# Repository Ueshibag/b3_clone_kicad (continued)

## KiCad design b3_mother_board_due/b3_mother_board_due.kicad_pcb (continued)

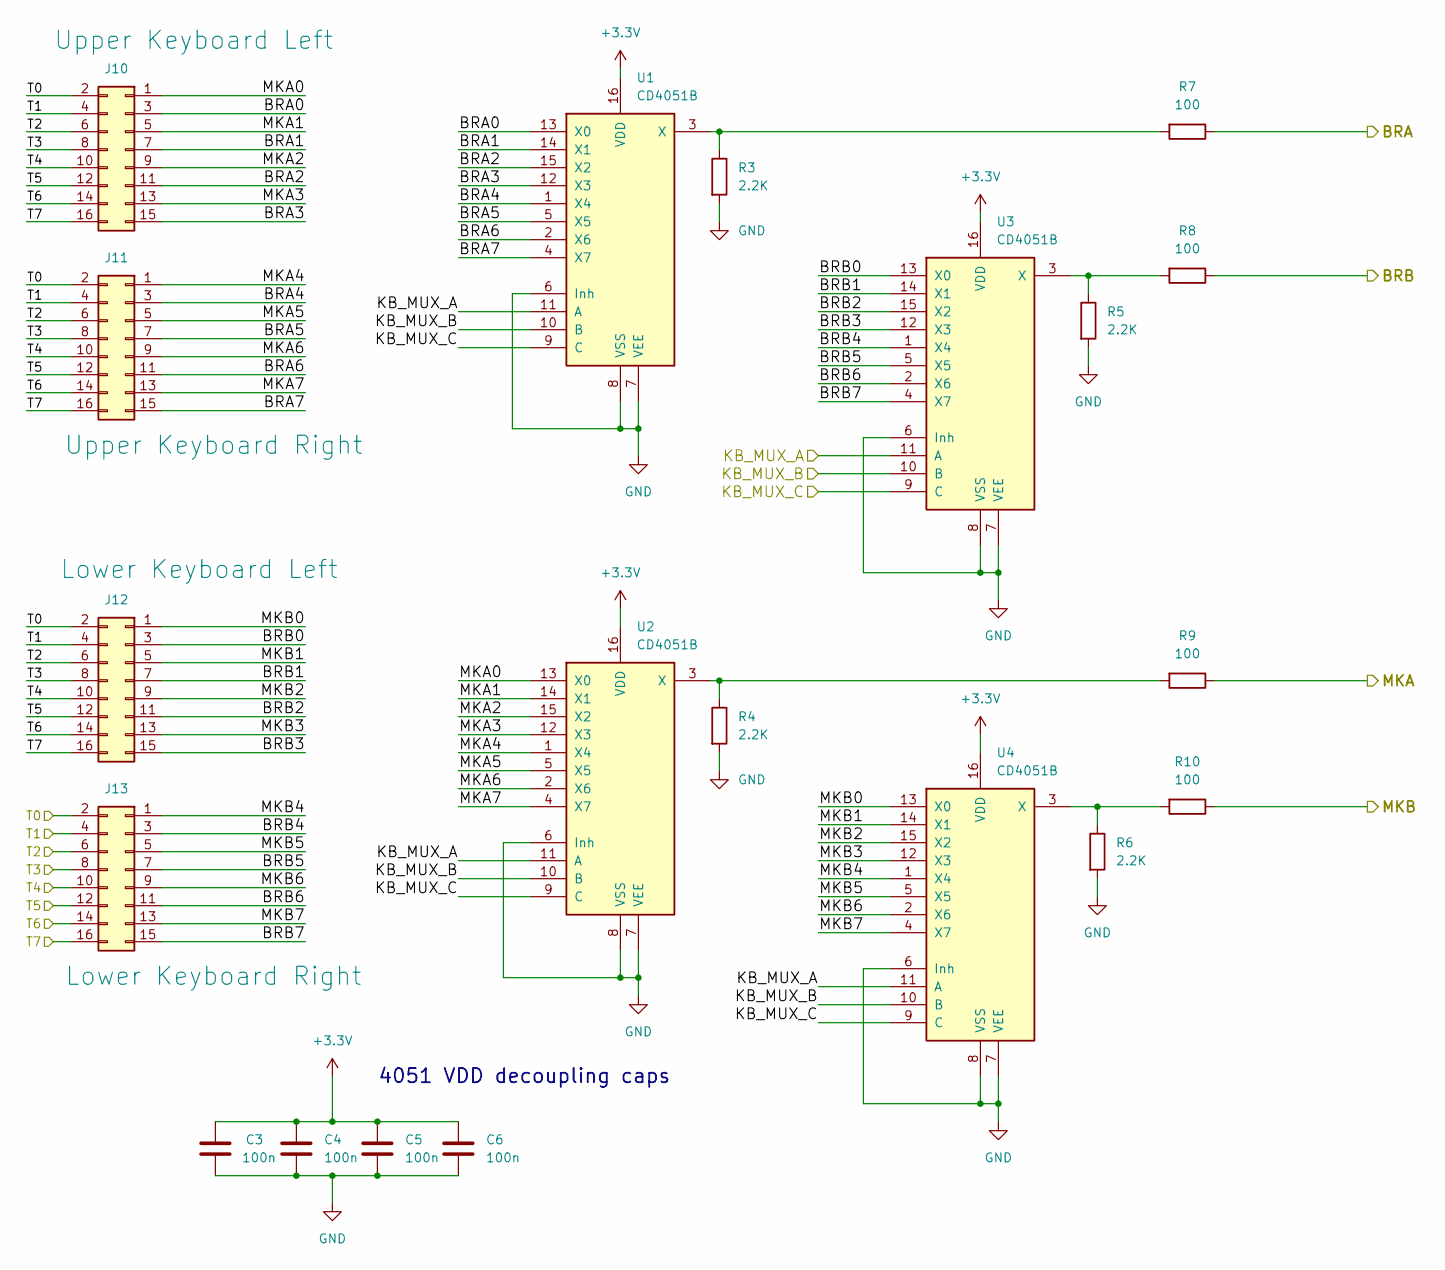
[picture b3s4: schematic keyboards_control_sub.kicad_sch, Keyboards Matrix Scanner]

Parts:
C3, C4, C5, C6: 100n; C_Rect_L11.5mm_W4.3mm_P10.00mm_MKT
J10: Upper Keyboard Left; IDC-Header_2x08_P2.54mm_Vertical
J11: Upper Keyboard Right; IDC-Header_2x08_P2.54mm_Vertical
J12: Lower Keyboard Left; IDC-Header_2x08_P2.54mm_Vertical
J13: Lower Keyboard Right; IDC-Header_2x08_P2.54mm_Vertical
R3, R4, R5, R6: 2.2K; R_Axial_DIN0207_L6.3mm_D2.5mm_P7.62mm_Horizontal
R7, R8, R9, R10: 100; R_Axial_DIN0207_L6.3mm_D2.5mm_P7.62mm_Horizontal
U1, U2, U3, U4: CD4051B; DIP-16_W7.62mm

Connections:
+3.3V: C3.1, C4.1, C5.1, C6.1, U1.16 (VDD), U2.16 (VDD), U3.16 (VDD), U4.16 (VDD); also elsewhere on the board
/T0: J10.2, J11.2, J12.2, J13.2; also elsewhere on the board
/T1: J10.4, J11.4, J12.4, J13.4; also elsewhere on the board
/T2: J10.6, J11.6, J12.6, J13.6; also elsewhere on the board
/T3: J10.8, J11.8, J12.8, J13.8; also elsewhere on the board
/T4: J10.10, J11.10, J12.10, J13.10; also elsewhere on the board
/T5: J10.12, J11.12, J12.12, J13.12; also elsewhere on the board
/T6: J10.14, J11.14, J12.14, J13.14; also elsewhere on the board
/T7: J10.16, J11.16, J12.16, J13.16; also elsewhere on the board
/keyboards_control_sub/BRA: R7.1; also elsewhere on the board
/keyboards_control_sub/BRA0: J10.3, U1.13 (X0)
/keyboards_control_sub/BRA1: J10.7, U1.14 (X1)
/keyboards_control_sub/BRA2: J10.11, U1.15 (X2)
/keyboards_control_sub/BRA3: J10.15, U1.12 (X3)
/keyboards_control_sub/BRA4: J11.3, U1.1 (X4)
/keyboards_control_sub/BRA5: J11.7, U1.5 (X5)
/keyboards_control_sub/BRA6: J11.11, U1.2 (X6)
/keyboards_control_sub/BRA7: J11.15, U1.4 (X7)
/keyboards_control_sub/BRB: R8.1; also elsewhere on the board
/keyboards_control_sub/BRB0: J12.3, U3.13 (X0)
/keyboards_control_sub/BRB1: J12.7, U3.14 (X1)
/keyboards_control_sub/BRB2: J12.11, U3.15 (X2)
/keyboards_control_sub/BRB3: J12.15, U3.12 (X3)
/keyboards_control_sub/BRB4: J13.3, U3.1 (X4)
/keyboards_control_sub/BRB5: J13.7, U3.5 (X5)
/keyboards_control_sub/BRB6: J13.11, U3.2 (X6)
/keyboards_control_sub/BRB7: J13.15, U3.4 (X7)
/keyboards_control_sub/KB_MUX_A: U1.11 (A), U2.11 (A), U3.11 (A), U4.11 (A); also elsewhere on the board
/keyboards_control_sub/KB_MUX_B: U1.10 (B), U2.10 (B), U3.10 (B), U4.10 (B); also elsewhere on the board
/keyboards_control_sub/KB_MUX_C: U1.9 (C), U2.9 (C), U3.9 (C), U4.9 (C); also elsewhere on the board
/keyboards_control_sub/MKA: R9.1; also elsewhere on the board
/keyboards_control_sub/MKA0: J10.1, U2.13 (X0)
/keyboards_control_sub/MKA1: J10.5, U2.14 (X1)
/keyboards_control_sub/MKA2: J10.9, U2.15 (X2)
/keyboards_control_sub/MKA3: J10.13, U2.12 (X3)
/keyboards_control_sub/MKA4: J11.1, U2.1 (X4)
/keyboards_control_sub/MKA5: J11.5, U2.5 (X5)
/keyboards_control_sub/MKA6: J11.9, U2.2 (X6)
/keyboards_control_sub/MKA7: J11.13, U2.4 (X7)
/keyboards_control_sub/MKB: R10.1; also elsewhere on the board
/keyboards_control_sub/MKB0: J12.1, U4.13 (X0)
/keyboards_control_sub/MKB1: J12.5, U4.14 (X1)
/keyboards_control_sub/MKB2: J12.9, U4.15 (X2)
/keyboards_control_sub/MKB3: J12.13, U4.12 (X3)
/keyboards_control_sub/MKB4: J13.1, U4.1 (X4)
/keyboards_control_sub/MKB5: J13.5, U4.5 (X5)
/keyboards_control_sub/MKB6: J13.9, U4.2 (X6)
/keyboards_control_sub/MKB7: J13.13, U4.4 (X7)
GND: C3.2, C4.2, C5.2, C6.2, R3.2, R4.2, R5.2, R6.2, U1.6 (Inh), U1.7 (VEE), U1.8 (VSS), U2.6 (Inh), U2.7 (VEE), U2.8 (VSS), U3.6 (Inh), U3.7 (VEE), U3.8 (VSS), U4.6 (Inh), U4.7 (VEE), U4.8 (VSS); also elsewhere on the board
unnamed: R3.1, R7.2, U1.3 (X)
unnamed: R4.1, R9.2, U2.3 (X)
unnamed: R5.1, R8.2, U3.3 (X)
unnamed: R6.1, R10.2, U4.3 (X)

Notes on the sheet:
4051 VDD decoupling caps

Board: 2 copper layers, 68 parts (0 on the bottom side), 113 nets, no tracks yet.

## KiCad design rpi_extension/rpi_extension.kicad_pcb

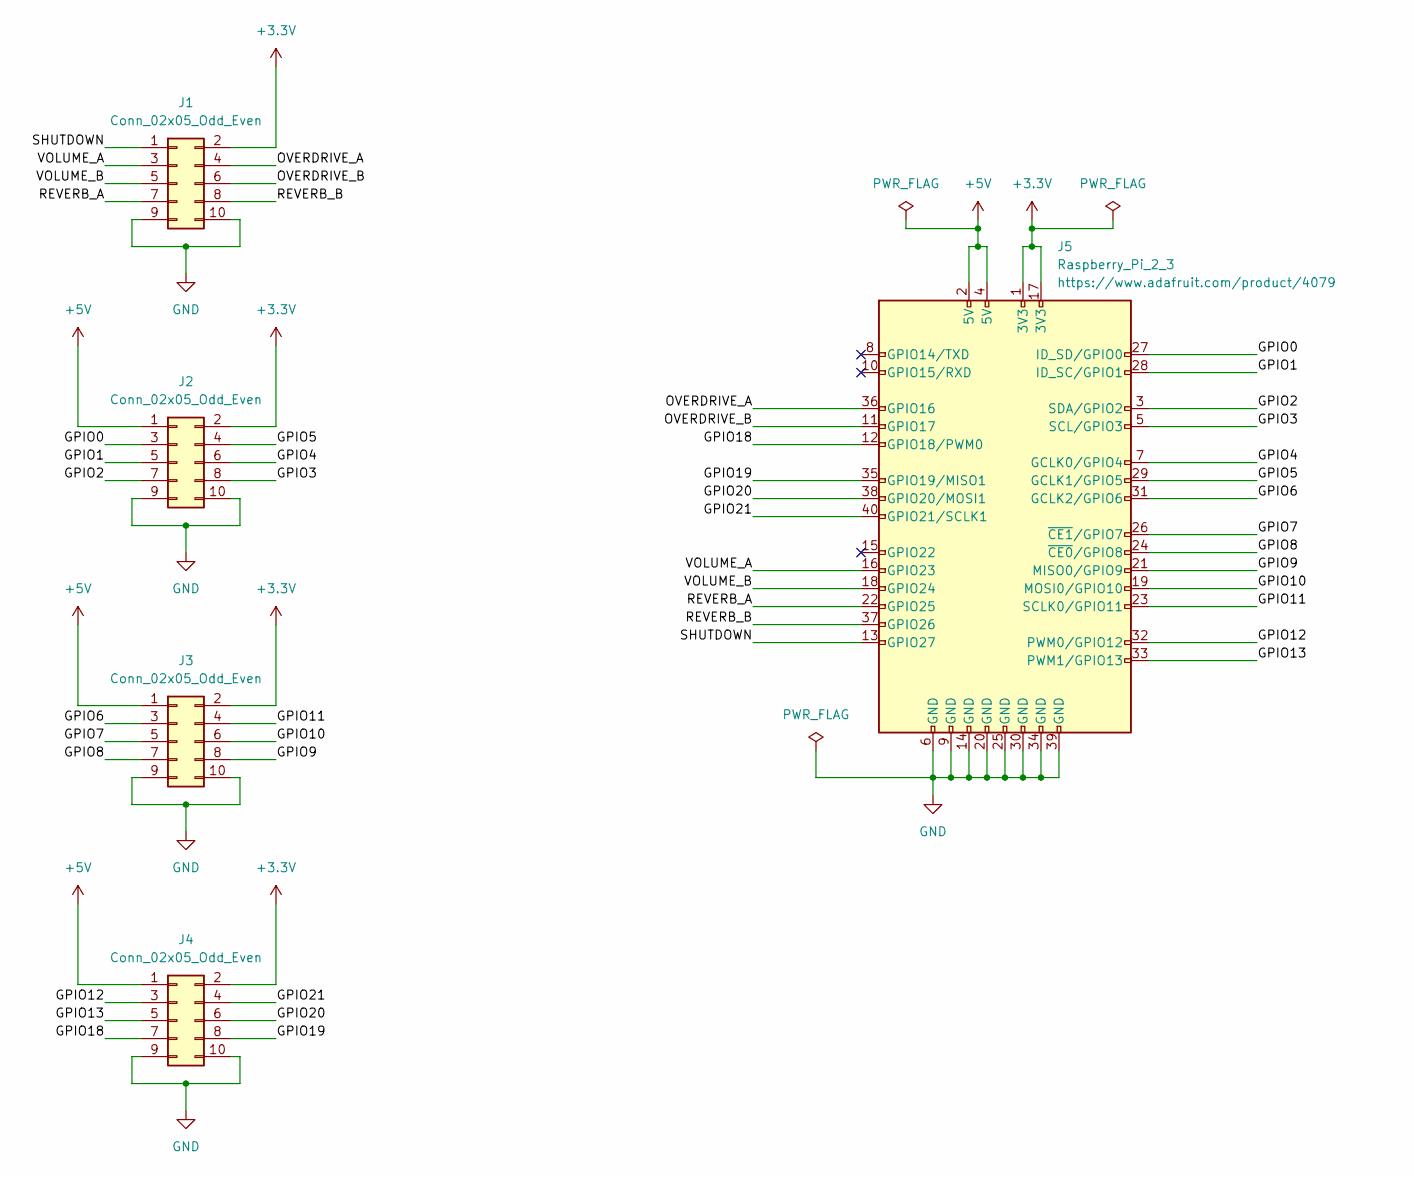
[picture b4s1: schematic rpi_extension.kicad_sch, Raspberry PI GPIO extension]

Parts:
J1, J2, J3, J4: Conn_02x05_Odd_Even; IDC-Header_2x05_P2.54mm_Horizontal
J5: Raspberry_Pi_2_3; PinSocket_2x20_P2.54mm_Vertical

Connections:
+3.3V: J1.2, J2.2, J3.2, J4.2, J5.1 (3V3), J5.17 (3V3)
+5V: J2.1, J3.1, J4.1, J5.2 (5V), J5.4 (5V)
/GPIO0: J2.3, J5.27 (ID_SD/GPIO0)
/GPIO1: J2.5, J5.28 (ID_SC/GPIO1)
/GPIO2: J2.7, J5.3 (SDA/GPIO2)
/GPIO3: J2.8, J5.5 (SCL/GPIO3)
/GPIO4: J2.6, J5.7 (GCLK0/GPIO4)
/GPIO5: J2.4, J5.29 (GCLK1/GPIO5)
/GPIO6: J3.3, J5.31 (GCLK2/GPIO6)
/GPIO7: J3.5, J5.26 (~CE1/GPIO7)
/GPIO8: J3.7, J5.24 (~CE0/GPIO8)
/GPIO9: J3.8, J5.21 (MISO0/GPIO9)
/GPIO10: J3.6, J5.19 (MOSI0/GPIO10)
/GPIO11: J3.4, J5.23 (SCLK0/GPIO11)
/GPIO12: J4.3, J5.32 (PWM0/GPIO12)
/GPIO13: J4.5, J5.33 (PWM1/GPIO13)
/GPIO18: J4.7, J5.12 (GPIO18/PWM0)
/GPIO19: J4.8, J5.35 (GPIO19/MISO1)
/GPIO20: J4.6, J5.38 (GPIO20/MOSI1)
/GPIO21: J4.4, J5.40 (GPIO21/SCLK1)
/OVERDRIVE_A: J1.4, J5.36 (GPIO16)
/OVERDRIVE_B: J1.6, J5.11 (GPIO17)
/REVERB_A: J1.7, J5.22 (GPIO25)
/REVERB_B: J1.8, J5.37 (GPIO26)
/SHUTDOWN: J1.1, J5.13 (GPIO27)
/VOLUME_A: J1.3, J5.16 (GPIO23)
/VOLUME_B: J1.5, J5.18 (GPIO24)
GND: J1.9, J1.10, J2.9, J2.10, J3.9, J3.10, J4.9, J4.10, J5.6 (GND), J5.9 (GND), J5.14 (GND), J5.20 (GND), J5.25 (GND), J5.30 (GND), J5.34 (GND), J5.39 (GND)

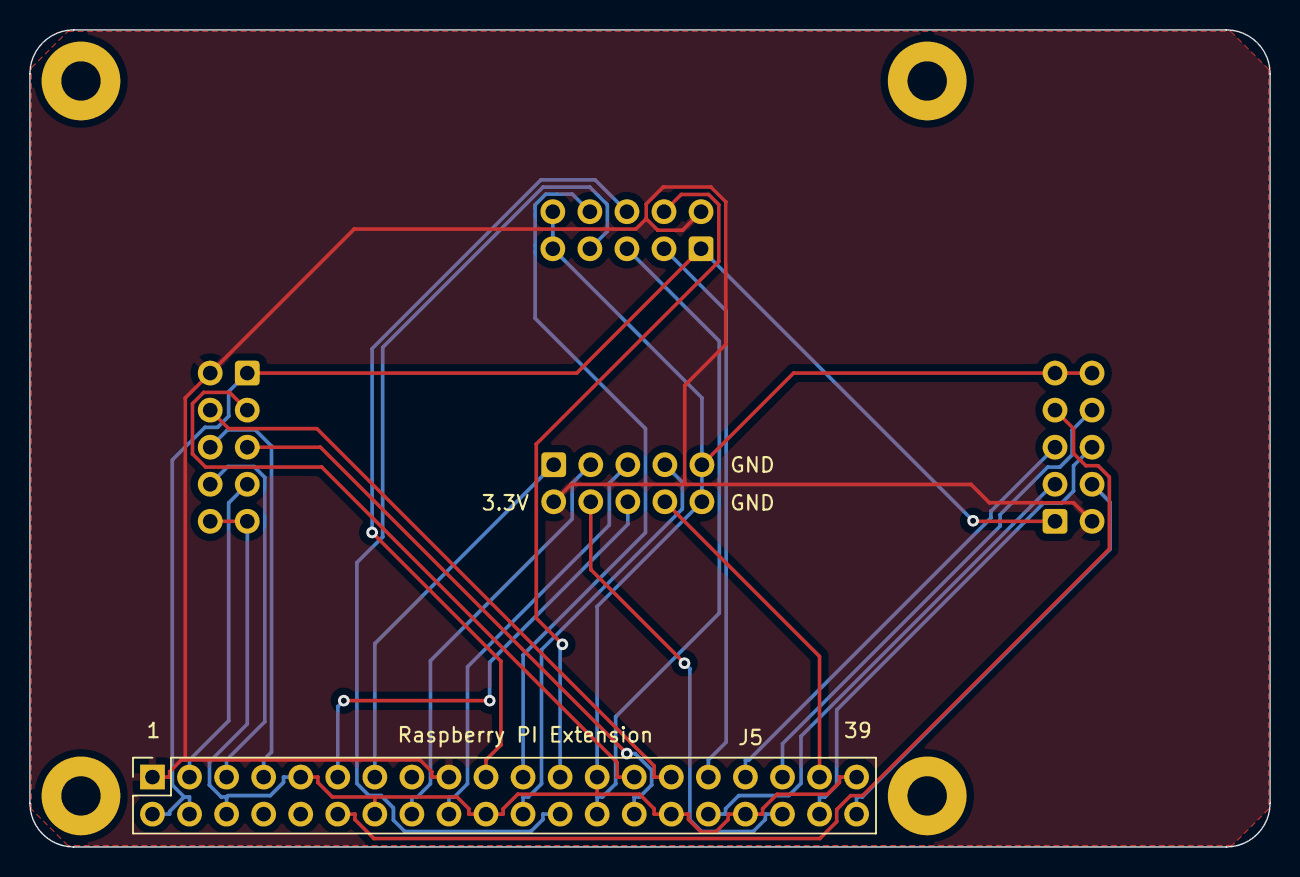
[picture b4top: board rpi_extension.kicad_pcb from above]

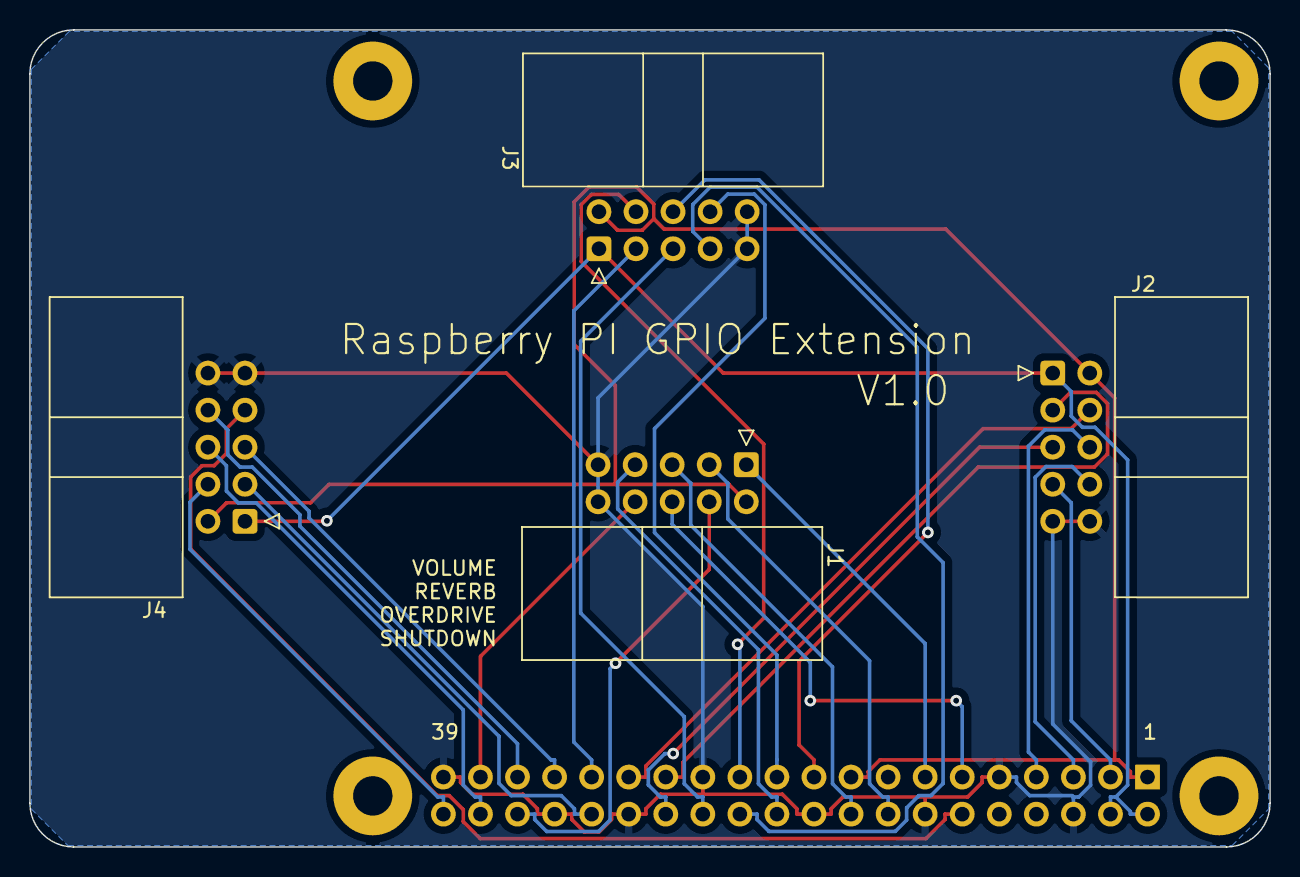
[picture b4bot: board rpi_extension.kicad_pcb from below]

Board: 2 copper layers, 85.0 x 56.0 mm, 9 parts (4 on the bottom side), 28 nets.

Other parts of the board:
REF1, REF2, REF3, REF4: MountingHole_2.7mm_Pad

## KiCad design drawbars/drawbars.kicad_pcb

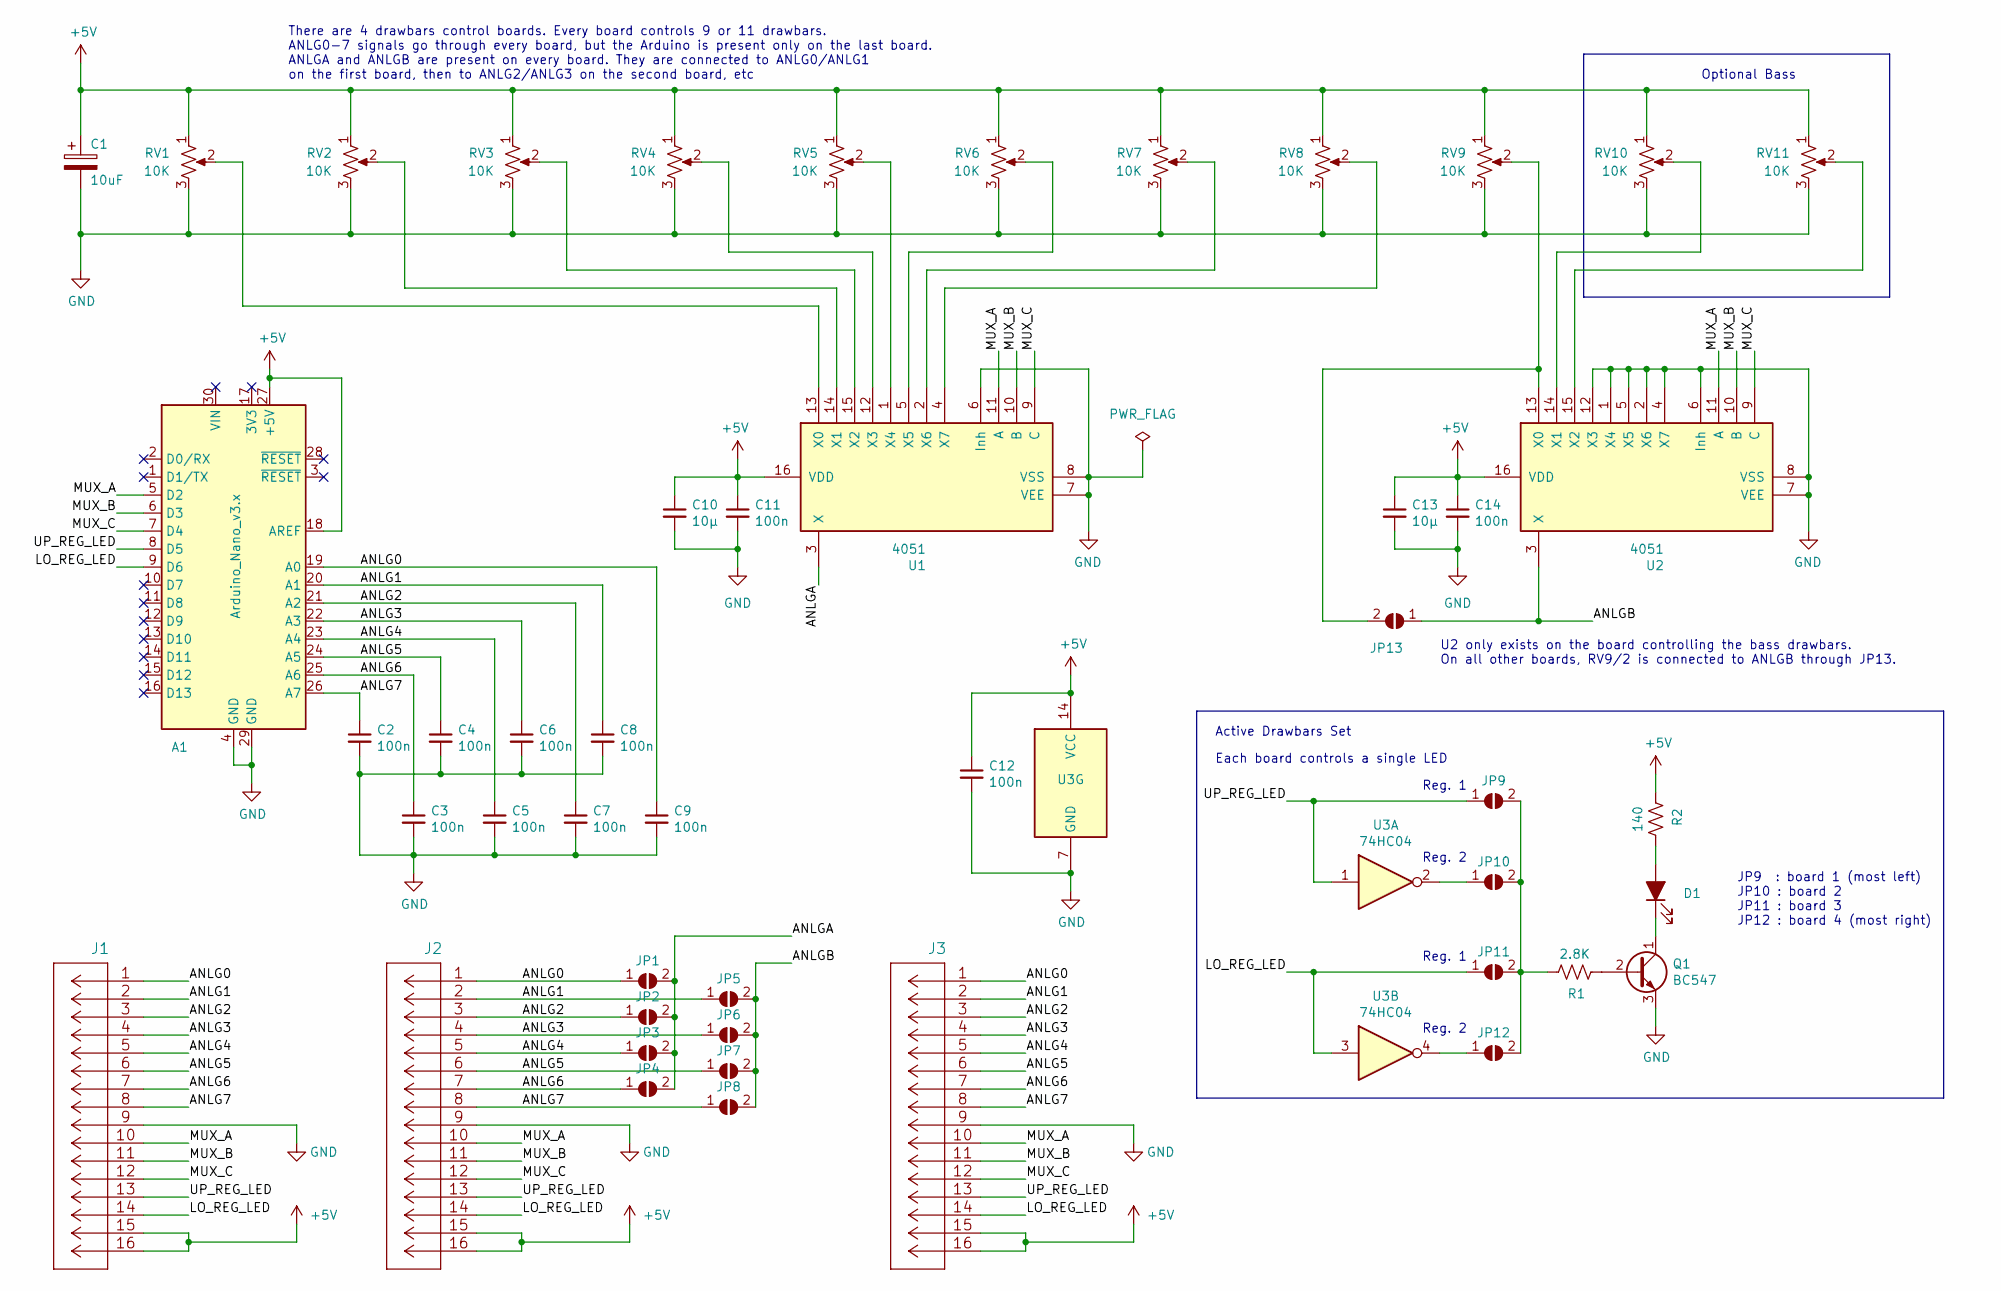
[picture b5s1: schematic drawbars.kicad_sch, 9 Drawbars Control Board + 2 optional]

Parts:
A1: Arduino_Nano_v3.x; Arduino_Nano
C1: 10uF; CP_Axial_L10.0mm_D4.5mm_P15.00mm_Horizontal
C2, C3, C4, C5, C6, C7, C8, C9, C11, C12, C14: 100n; C_1206_3216Metric_Pad1.33x1.80mm_HandSolder
C10, C13: 10µ; C_1206_3216Metric_Pad1.33x1.80mm_HandSolder
D1: LED_Filled; LED_D3.0mm_FlatTop
J1, J2, J3: 8-215079-6; MicroMatch_2x08_P1.27mm_Vertical
JP1, JP2, JP3, JP4, JP5, JP6, JP7, JP8, JP9, JP10, JP11, JP12, JP13: SolderJumper_2_Open; SolderJumper-2_P1.3mm_Open_RoundedPad1.0x1.5mm
Q1: BC547; TO-92_Inline
R1: 2.8K; R_1206_3216Metric_Pad1.30x1.75mm_HandSolder
R2: 140; R_1206_3216Metric_Pad1.30x1.75mm_HandSolder
RV1, RV2, RV3, RV4, RV5, RV6, RV7, RV8, RV9, RV10, RV11: 10K; Drawbar_Potentiometer
U1, U2: 4051; DIP-16_W7.62mm
U3: 74HC04; DIP-14_W7.62mm

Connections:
+5V: A1.18 (AREF), A1.27 (+5V), C1.1, C10.1, C11.1, C12.1, C13.1, C14.1, J1.15, J1.16, J2.15, J2.16, J3.15, J3.16, R2.2, RV1.1, RV2.1, RV3.1, RV4.1, RV5.1, RV6.1, RV7.1, RV8.1, RV9.1, RV10.1, RV11.1, U1.16 (VDD), U2.16 (VDD), U3.14 (VCC)
/ANLG0: A1.19 (A0), C9.1, J1.1, J2.1, J3.1, JP1.1 (A)
/ANLG1: A1.20 (A1), C8.1, J1.2, J2.2, J3.2, JP5.1 (A)
/ANLG2: A1.21 (A2), C7.1, J1.3, J2.3, J3.3, JP2.1 (A)
/ANLG3: A1.22 (A3), C6.1, J1.4, J2.4, J3.4, JP6.1 (A)
/ANLG4: A1.23 (A4), C5.1, J1.5, J2.5, J3.5, JP3.1 (A)
/ANLG5: A1.24 (A5), C4.1, J1.6, J2.6, J3.6, JP7.1 (A)
/ANLG6: A1.25 (A6), C3.1, J1.7, J2.7, J3.7, JP4.1 (A)
/ANLG7: A1.26 (A7), C2.1, J1.8, J2.8, J3.8, JP8.1 (A)
/ANLGA: JP1.2 (B), JP2.2 (B), JP3.2 (B), JP4.2 (B), U1.3 (X)
/ANLGB: JP5.2 (B), JP6.2 (B), JP7.2 (B), JP8.2 (B), JP13.1 (A), U2.3 (X)
/LO_REG_LED: A1.9 (D6), J1.14, J2.14, J3.14, JP11.1 (A), U3.3
/MUX_A: A1.5 (D2), J1.10, J2.10, J3.10, U1.11 (A), U2.11 (A)
/MUX_B: A1.6 (D3), J1.11, J2.11, J3.11, U1.10 (B), U2.10 (B)
/MUX_C: A1.7 (D4), J1.12, J2.12, J3.12, U1.9 (C), U2.9 (C)
/UP_REG_LED: A1.8 (D5), J1.13, J2.13, J3.13, JP9.1 (A), U3.1
GND: A1.4 (GND), A1.29 (GND), C1.2, C2.2, C3.2, C4.2, C5.2, C6.2, C7.2, C8.2, C9.2, C10.2, C11.2, C12.2, C13.2, C14.2, J1.9, J2.9, J3.9, Q1.3 (E), RV1.3, RV2.3, RV3.3, RV4.3, RV5.3, RV6.3, RV7.3, RV8.3, RV9.3, RV10.3, RV11.3, U1.6 (Inh), U1.7 (VEE), U1.8 (VSS), U2.1 (X4), U2.2 (X6), U2.4 (X7), U2.5 (X5), U2.6 (Inh), U2.7 (VEE), U2.8 (VSS), U2.12 (X3), U3.7 (GND)
unnamed: D1.1 (K), Q1.1 (C)
unnamed: D1.2 (A), R2.1
unnamed: JP10.1 (A), U3.2
unnamed: JP9.2 (B), JP10.2 (B), JP11.2 (B), JP12.2 (B), R1.1
unnamed: JP12.1 (A), U3.4
unnamed: JP13.2 (B), RV9.2, U2.13 (X0)
unnamed: Q1.2 (B), R1.2
unnamed: RV1.2, U1.13 (X0)
unnamed: RV2.2, U1.14 (X1)
unnamed: RV3.2, U1.15 (X2)
unnamed: RV4.2, U1.12 (X3)
unnamed: RV5.2, U1.1 (X4)
unnamed: RV6.2, U1.5 (X5)
unnamed: RV7.2, U1.2 (X6)
unnamed: RV8.2, U1.4 (X7)
unnamed: RV10.2, U2.14 (X1)
unnamed: RV11.2, U2.15 (X2)

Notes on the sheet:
Reg. 2
Optional Bass
Each board controls a single LED
Reg. 1
JP9 : board 1 (most left) JP10 : board 2 JP11 : board 3 JP12 : board 4 (most right)
Active Drawbars Set
U2 only exists on the board controlling the bass drawbars. On all other boards, RV9/2 is connected to ANLGB through JP13.
There are 4 drawbars control boards. Every board controls 9 or 11 drawbars. ANLG0-7 signals go through every board, but the Arduino is present only on the last board. ANLGA and ANLGB are present on every board. They are connected to ANLG0/ANLG1 on the first board, then to ANLG2/ANLG3 on the second 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

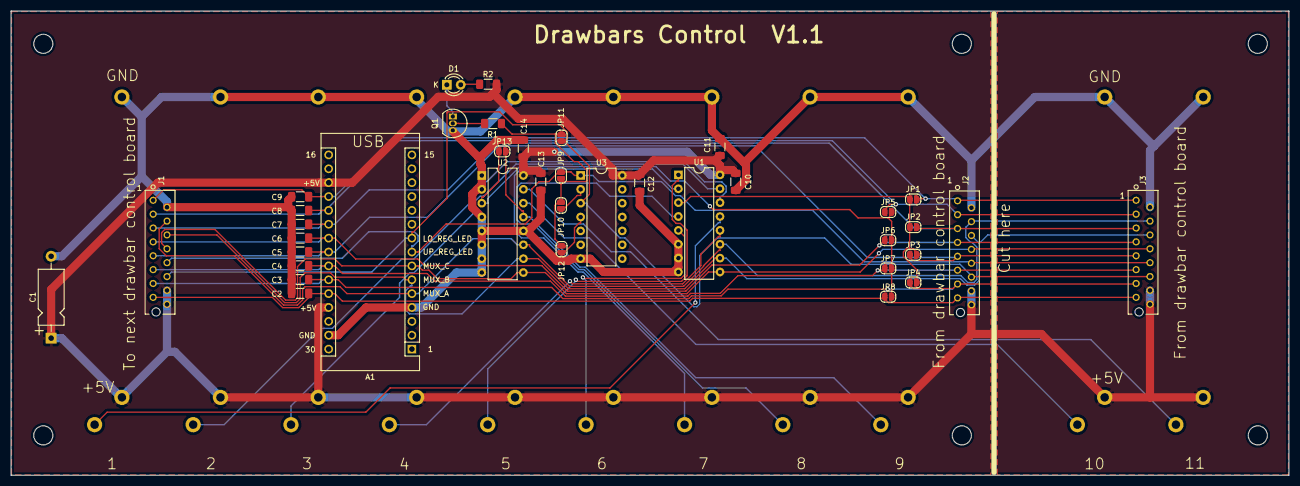
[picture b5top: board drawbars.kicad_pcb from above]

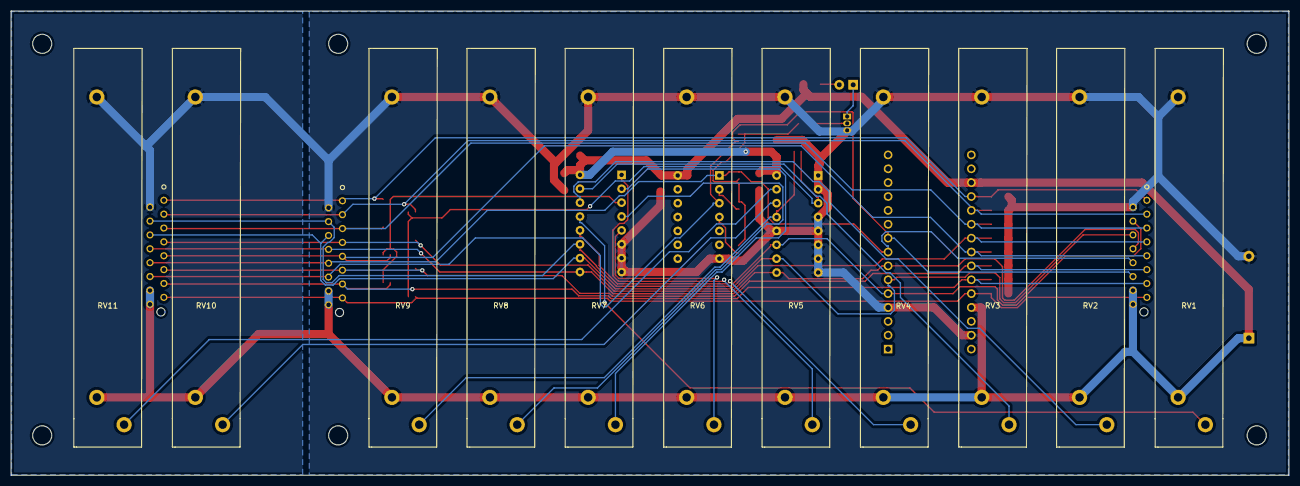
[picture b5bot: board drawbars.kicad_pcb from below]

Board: 2 copper layers, 234.0 x 85.0 mm, 55 parts (11 on the bottom side), 34 nets.

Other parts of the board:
REF1, REF2, REF3, REF4, REF5, REF6: MountingHole_3.5mm

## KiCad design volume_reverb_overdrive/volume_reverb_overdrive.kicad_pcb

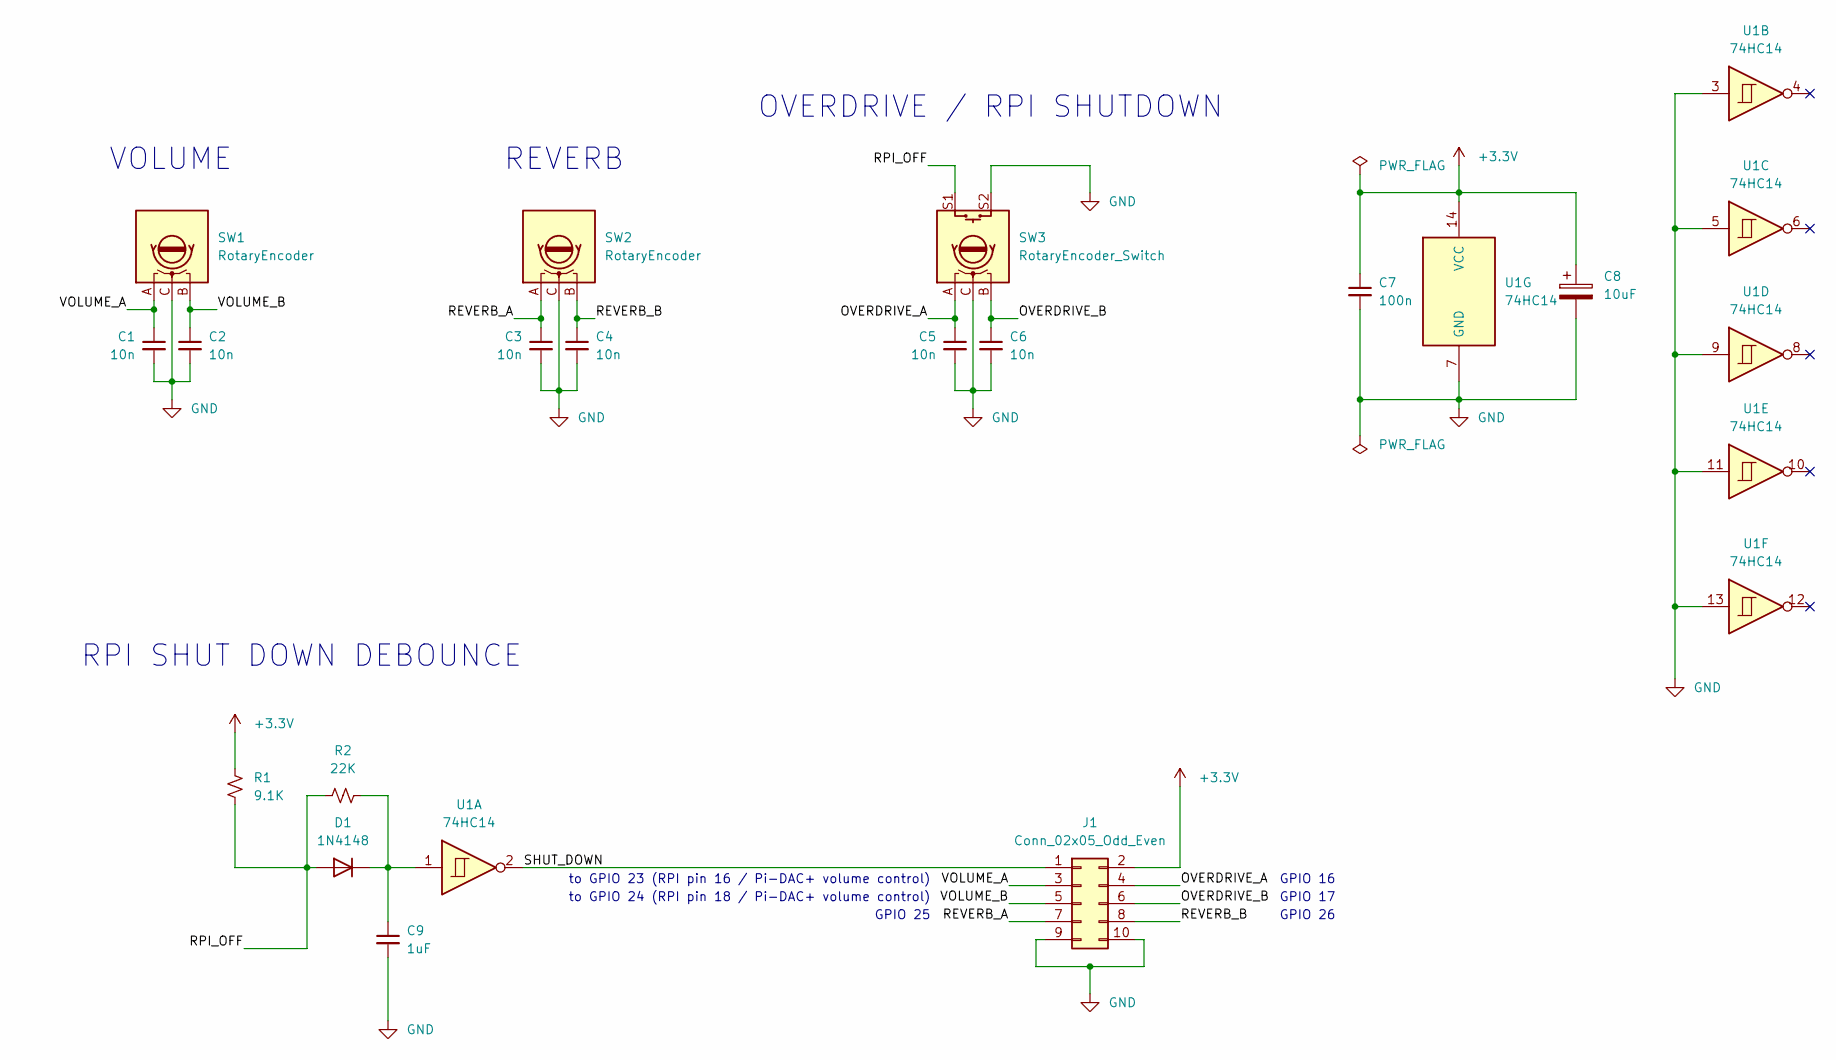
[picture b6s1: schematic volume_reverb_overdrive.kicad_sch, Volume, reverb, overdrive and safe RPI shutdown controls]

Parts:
C1, C2, C3, C4, C5, C6: 10n; C_1206_3216Metric_Pad1.33x1.80mm_HandSolder
C7: 100n; C_1206_3216Metric_Pad1.33x1.80mm_HandSolder
C8: 10uF; CP_Radial_D5.0mm_P2.00mm
C9: 1uF; C_1206_3216Metric_Pad1.33x1.80mm_HandSolder
D1: 1N4148; D_DO-35_SOD27_P7.62mm_Horizontal
J1: Conn_02x05_Odd_Even; IDC-Header_2x05_P2.54mm_Vertical
R1: 9.1K; R_1206_3216Metric_Pad1.30x1.75mm_HandSolder
R2: 22K; R_1206_3216Metric_Pad1.30x1.75mm_HandSolder
SW1, SW2: RotaryEncoder; RotaryEncoder_Alps_EC11E-Switch_Vertical_H20mm
SW3: RotaryEncoder_Switch; RotaryEncoder_Alps_EC11E-Switch_Vertical_H20mm
U1: 74HC14; DIP-14_W7.62mm

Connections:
+3.3V: C7.1, C8.1, J1.2, R1.1, U1.14 (VCC)
/OVERDRIVE_A: C5.1, J1.4, SW3.A
/OVERDRIVE_B: C6.1, J1.6, SW3.B
/REVERB_A: C3.1, J1.7, SW2.A
/REVERB_B: C4.1, J1.8, SW2.B
/RPI_OFF: D1.2 (A), R1.2, R2.2, SW3.S1
/SHUT_DOWN: J1.1, U1.2
/VOLUME_A: C1.1, J1.3, SW1.A
/VOLUME_B: C2.1, J1.5, SW1.B
GND: C1.2, C2.2, C3.2, C4.2, C5.2, C6.2, C7.2, C8.2, C9.2, J1.9, J1.10, SW1.C, SW2.C, SW3.C, SW3.S2, U1.3, U1.5, U1.7 (GND), U1.9, U1.11, U1.13
unnamed: C9.1, D1.1 (K), R2.1, U1.1

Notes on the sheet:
GPIO 17
RPI SHUT DOWN DEBOUNCE
REVERB
GPIO 25
to GPIO 24 (RPI pin 18 / Pi-DAC+ volume control)
OVERDRIVE / RPI SHUTDOWN
to GPIO 23 (RPI pin 16 / Pi-DAC+ volume control)
VOLUME
GPIO 26
GPIO 16

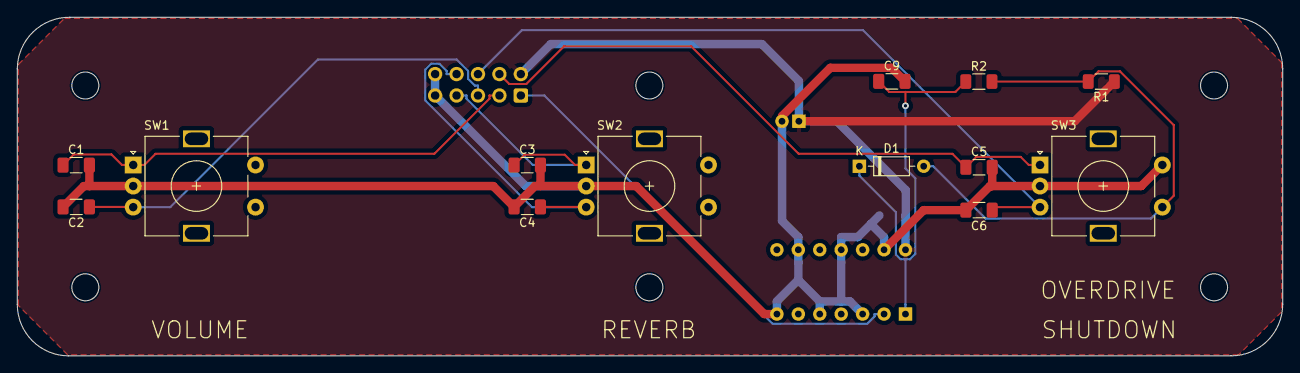
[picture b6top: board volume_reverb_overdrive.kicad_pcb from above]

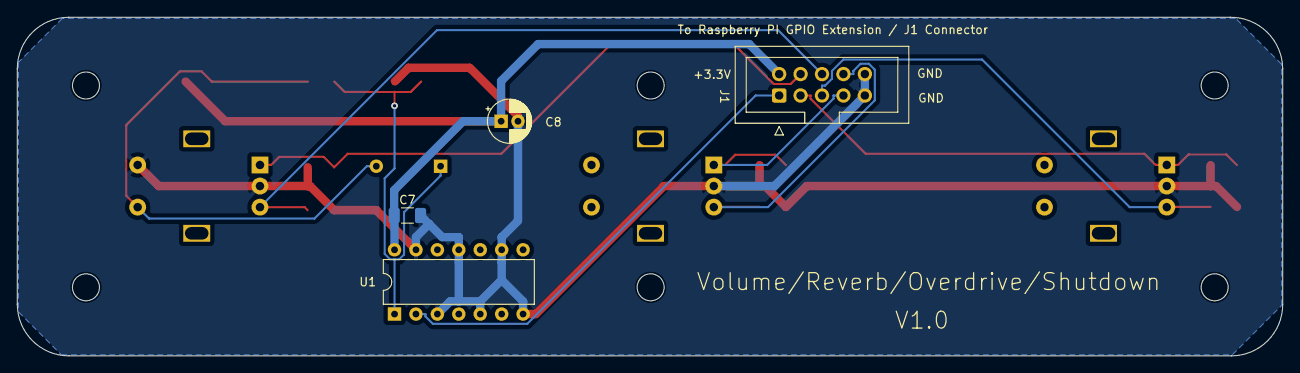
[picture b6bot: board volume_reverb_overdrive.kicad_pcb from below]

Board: 2 copper layers, 150.0 x 40.1 mm, 23 parts (4 on the bottom side), 11 nets.

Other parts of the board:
REF1, REF2, REF3, REF4, REF5, REF6: MountingHole_3.2mm_M3

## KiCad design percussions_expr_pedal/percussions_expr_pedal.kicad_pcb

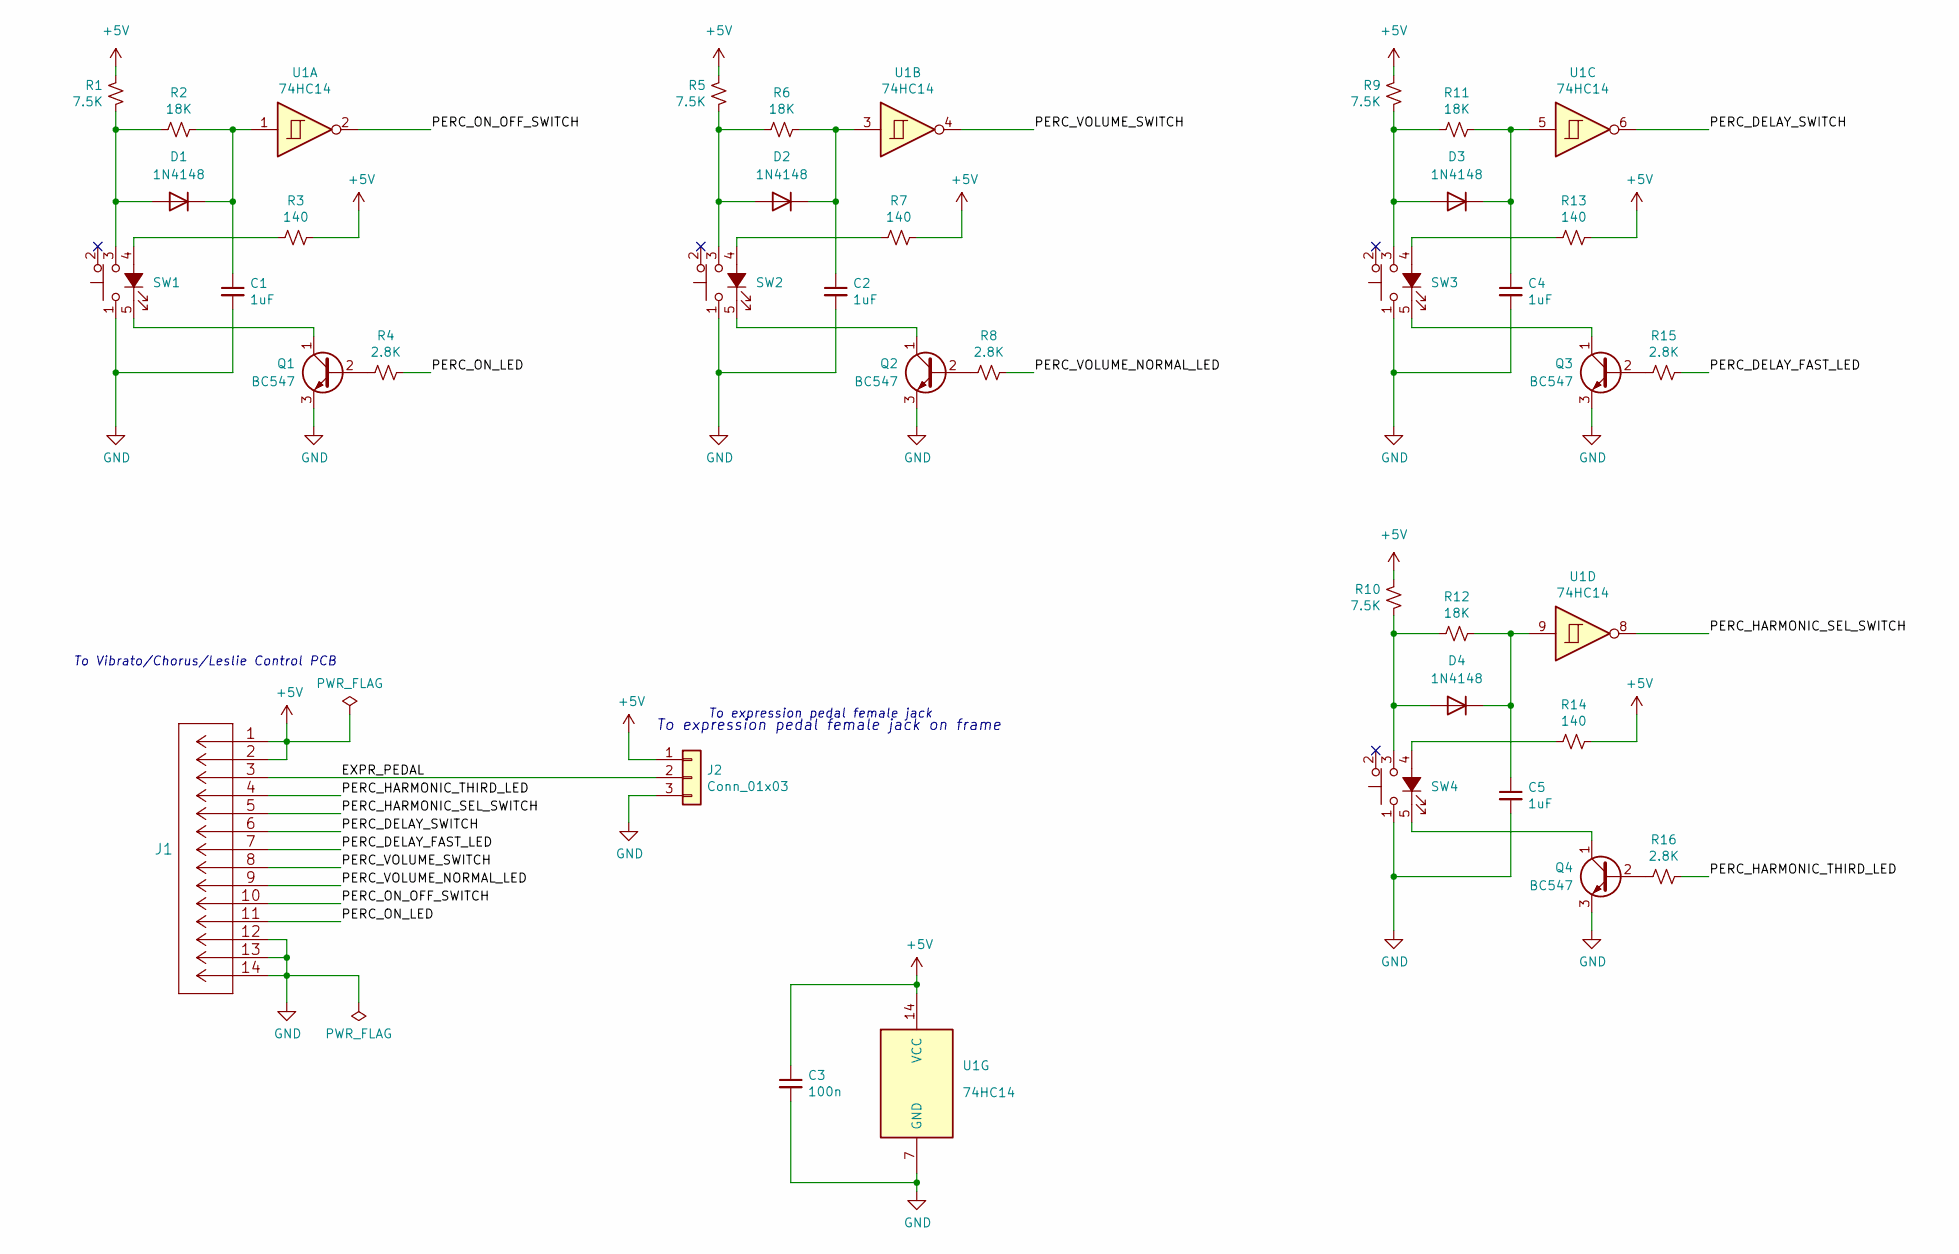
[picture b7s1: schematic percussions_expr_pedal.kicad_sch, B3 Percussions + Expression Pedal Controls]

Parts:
C1, C2, C4, C5: 1uF; C_1206_3216Metric_Pad1.33x1.80mm_HandSolder
C3: 100n; C_1206_3216Metric_Pad1.33x1.80mm_HandSolder
D1, D2, D3, D4: 1N4148; D_DO-35_SOD27_P7.62mm_Horizontal
J1: 8-215079-4; MicroMatch_2x07_P1.27mm_Vertical
J2: Conn_01x03; PinHeader_1x03_P2.54mm_Vertical
Q1, Q2, Q3, Q4: BC547; TO-92_Inline
R1, R5, R9, R10: 7.5K; R_1206_3216Metric_Pad1.30x1.75mm_HandSolder
R2, R6, R11, R12: 18K; R_1206_3216Metric_Pad1.30x1.75mm_HandSolder
R3, R7, R13, R14: 140; R_1206_3216Metric_Pad1.30x1.75mm_HandSolder
R4, R8, R15, R16: 2.8K; R_1206_3216Metric_Pad1.30x1.75mm_HandSolder
SW1, SW2, SW3, SW4: E-SWITCH-SW_Push_LED; 5511MBLKRED
U1: 74HC14; SOIC-14_3.9x8.7mm_P1.27mm

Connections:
+5V: C3.1, J1.1, J1.2, J2.1, R1.1, R3.1, R5.1, R7.1, R9.1, R10.1, R13.1, R14.1, U1.14 (VCC)
/EXPR_PEDAL: J1.3, J2.2
/PERC_DELAY_FAST_LED: J1.7, R15.1
/PERC_DELAY_SWITCH: J1.6, U1.6
/PERC_HARMONIC_SEL_SWITCH: J1.5, U1.8
/PERC_HARMONIC_THIRD_LED: J1.4, R16.1
/PERC_ON_LED: J1.11, R4.1
/PERC_ON_OFF_SWITCH: J1.10, U1.2
/PERC_VOLUME_NORMAL_LED: J1.9, R8.1
/PERC_VOLUME_SWITCH: J1.8, U1.4
GND: C1.2, C2.2, C3.2, C4.2, C5.2, J1.12, J1.13, J1.14, J2.3, Q1.3 (E), Q2.3 (E), Q3.3 (E), Q4.3 (E), SW1.1, SW2.1, SW3.1, SW4.1, U1.7 (GND)
unnamed: C1.1, D1.1 (K), R2.1, U1.1
unnamed: C2.1, D2.1 (K), R6.1, U1.3
unnamed: C4.1, D3.1 (K), R11.1, U1.5
unnamed: C5.1, D4.1 (K), R12.1, U1.9
unnamed: D1.2 (A), R1.2, R2.2, SW1.3
unnamed: D2.2 (A), R5.2, R6.2, SW2.3
unnamed: D3.2 (A), R9.2, R11.2, SW3.3
unnamed: D4.2 (A), R10.2, R12.2, SW4.3
unnamed: Q1.1 (C), SW1.5 (K)
unnamed: Q1.2 (B), R4.2
unnamed: Q2.1 (C), SW2.5 (K)
unnamed: Q2.2 (B), R8.2
unnamed: Q3.1 (C), SW3.5 (K)
unnamed: Q3.2 (B), R15.2
unnamed: Q4.1 (C), SW4.5 (K)
unnamed: Q4.2 (B), R16.2
unnamed: R3.2, SW1.4 (A)
unnamed: R7.2, SW2.4 (A)
unnamed: R13.2, SW3.4 (A)
unnamed: R14.2, SW4.4 (A)

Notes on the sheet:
To expression pedal female jack on frame
To expression pedal female jack
To Vibrato/Chorus/Leslie Control PCB
